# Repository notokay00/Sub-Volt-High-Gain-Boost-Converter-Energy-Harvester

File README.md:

# Sub-Volt TEG Energy Harvesting Boost Converter (BQ25504)

This repository contains the KiCad 8.0 hardware design, TINA-TI transient simulations, and project documentation for a sub-volt thermoelectric generator (TEG) energy harvesting boost converter. 

Designed around the Texas Instruments **BQ25504** ultra-low-power harvester, this circuit steps up 300mV–600mV DC inputs to a regulated 3.30V to intermittently power an ESP32-C3 telemetry load from a 10mF supercapacitor. While tested with a TEG, the sub-volt architecture is designed as an analog to evaluate power extraction from low-yield sources like Carbon-14 betavoltaic cells.

## ⚡ System Architecture & Specifications
* **Harvester IC:** Texas Instruments BQ25504 (330 nA quiescent current).
* **Cold-Start Voltage:** $\ge 330\text{ mV}$ (steps up from zero using an internal high-frequency oscillator and external $22\ \mu\text{H}$ inductor).
* **MPPT Network:** 50% Fractional Open-Circuit Voltage tracking for maximum power transfer, sampled every 16 seconds.
* **Storage Element:** 10 mF radial supercapacitor, providing 33.64 mJ of usable energy per discharge cycle.
* **Voltage Thresholds (Megaohm Dividers):**
  * Overvoltage Cutoff ($V_{\text{OV}}$): $\sim 3.30\text{ V}$ (protects the supercapacitor and load).
  * Undervoltage Cutoff ($V_{\text{UV}}$): $\sim 2.04\text{ V}.

## 🛠️ Hardware Design (sikhi_v1)
The 2-layer FR4 PCB measures 33.35 mm × 25.80 mm and was designed in KiCad 8.0 with strict analog layout rules:
* **Switching Node Isolation:** The noisy $22\ \mu\text{H}$ inductor switching loop is physically partitioned away from the high-impedance $10\text{ M}\Omega$ MPPT and threshold sensing dividers to prevent capacitive crosstalk.
* **Thermal Grounding:** The BQ25504 VQFN-16 exposed pad is stitched to an unbroken bottom ground plane using four $0.20\text{ mm}$ thermal vias for a low-impedance return path.
* **High-Frequency Bypassing:** A $100\text{ nF}$ low-ESL ceramic capacitor is placed immediately adjacent to the `VSTOR` pin to shunt MHz switching harmonics.
* **Assembly:** Designed for automated turnkey assembly (PCBA) using generated Pick & Place (CPL) and BOM files to prevent VQFN-16 package floating.

## 📂 Repository Contents
* `/Hardware/`: KiCad 8.0 schematic, PCB layout (`sikhi_v1`), and production-ready Gerber (.gbr) / Excellon drill (.drl) files.
* `/Simulation/`: TINA-TI transient SPICE models demonstrating the cold-start ramp, supercapacitor voltage coupling, and 64ms Nano-Power `VRDIV` sampling pulses.
* `/Docs/`: Final engineering report, component design calculations, layout verification, and manufacturing Bill of Materials.

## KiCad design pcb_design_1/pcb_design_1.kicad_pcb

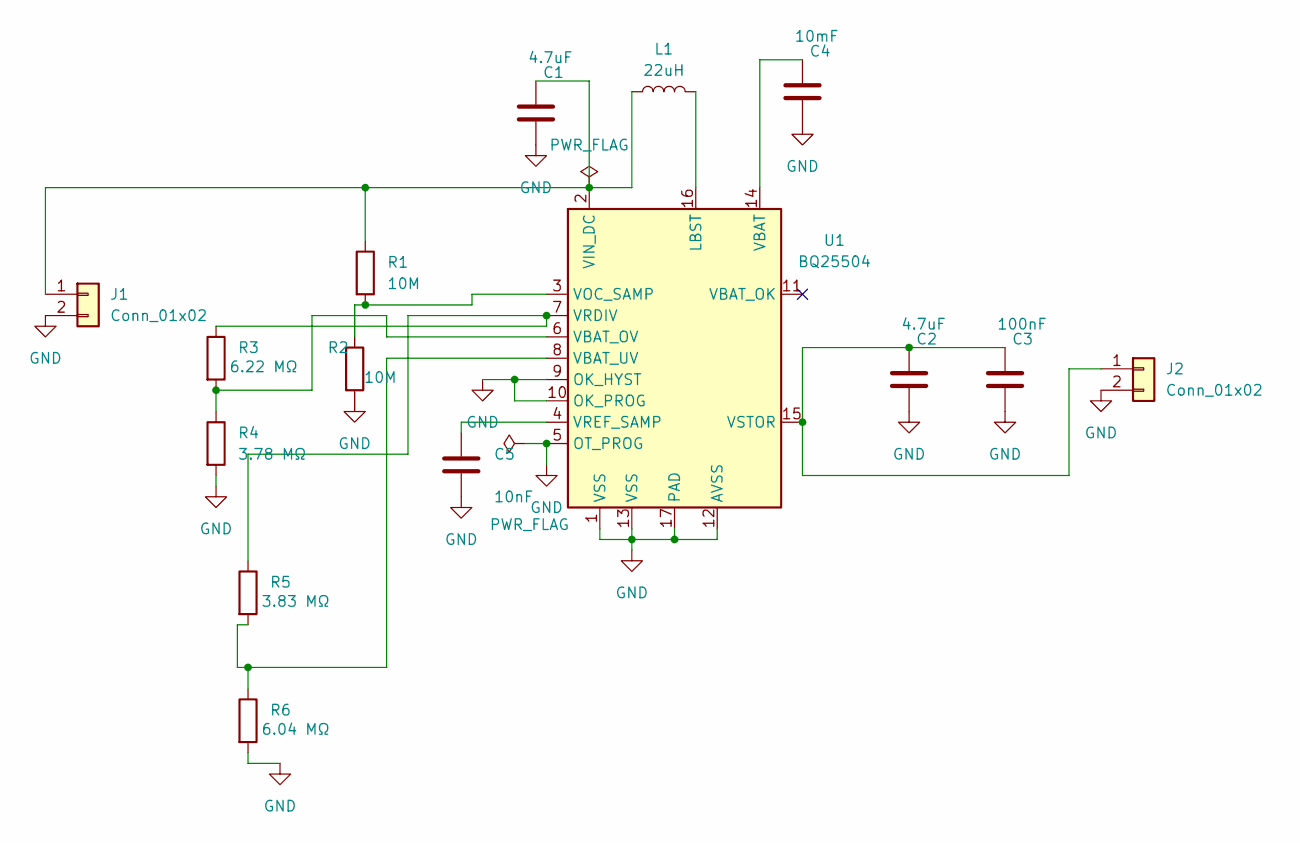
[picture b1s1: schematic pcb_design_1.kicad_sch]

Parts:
C1, C2: 4.7uF; C_0805_2012Metric
C3: 100nF; C_0603_1608Metric
C4: 10mF; CP_Radial_D10.0mm_P5.00mm
C5: 10nF; C_0603_1608Metric
J1, J2: Conn_01x02; TerminalBlock_Phoenix_PT-1,5-2-3.5-H_1x02_P3.50mm_Horizontal
L1: 22uH; L_Taiyo-Yuden_MD-4040
R1, R2: 10M; R_0805_2012Metric
R3: 6.22 MΩ; R_0805_2012Metric
R4: 3.78 MΩ; R_0805_2012Metric
R5: 3.83 MΩ; R_0805_2012Metric
R6: 6.04 MΩ; R_0805_2012Metric
U1: BQ25504; VQFN-16-1EP_3x3mm_P0.5mm_EP1.68x1.68mm_ThermalVias

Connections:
GND: C1.2, C2.2, C3.2, C4.2, C5.2, J1.2, J2.2, R2.2, R4.2, R6.2, U1.1 (VSS), U1.5 (OT_PROG), U1.9 (OK_HYST), U1.10 (OK_PROG), U1.12 (AVSS), U1.13 (VSS), U1.17 (PAD)
unnamed: C1.1, J1.1, L1.1, R1.1, U1.2 (VIN_DC)
unnamed: C2.1, C3.1, J2.1, U1.15 (VSTOR)
unnamed: L1.2, U1.16 (LBST)
unnamed: C4.1, U1.14 (VBAT)
unnamed: R3.2, R4.1, U1.6 (VBAT_OV)
unnamed: R5.2, R6.1, U1.8 (VBAT_UV)
unnamed: R1.2, R2.1, U1.3 (VOC_SAMP)
unnamed: R3.1, R5.1, U1.7 (VRDIV)
unnamed: C5.1, U1.4 (VREF_SAMP)

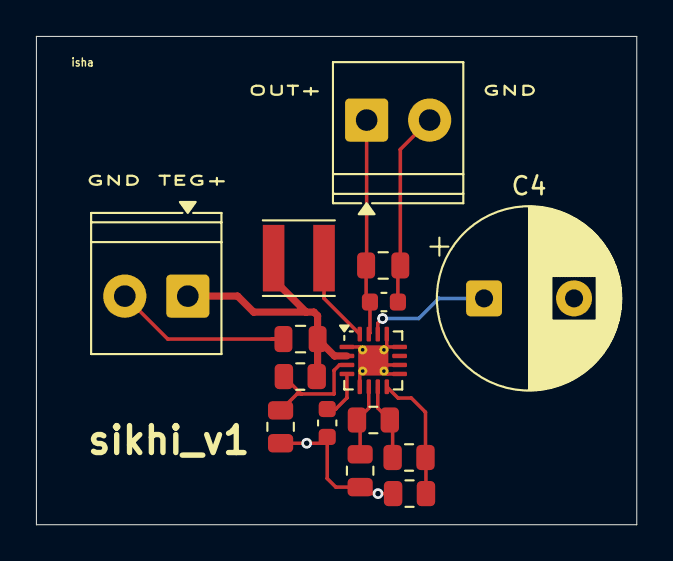
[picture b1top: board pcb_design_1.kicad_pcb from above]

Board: 2 copper layers, 33.4 x 27.1 mm, 15 parts (0 on the bottom side), 10 nets.
